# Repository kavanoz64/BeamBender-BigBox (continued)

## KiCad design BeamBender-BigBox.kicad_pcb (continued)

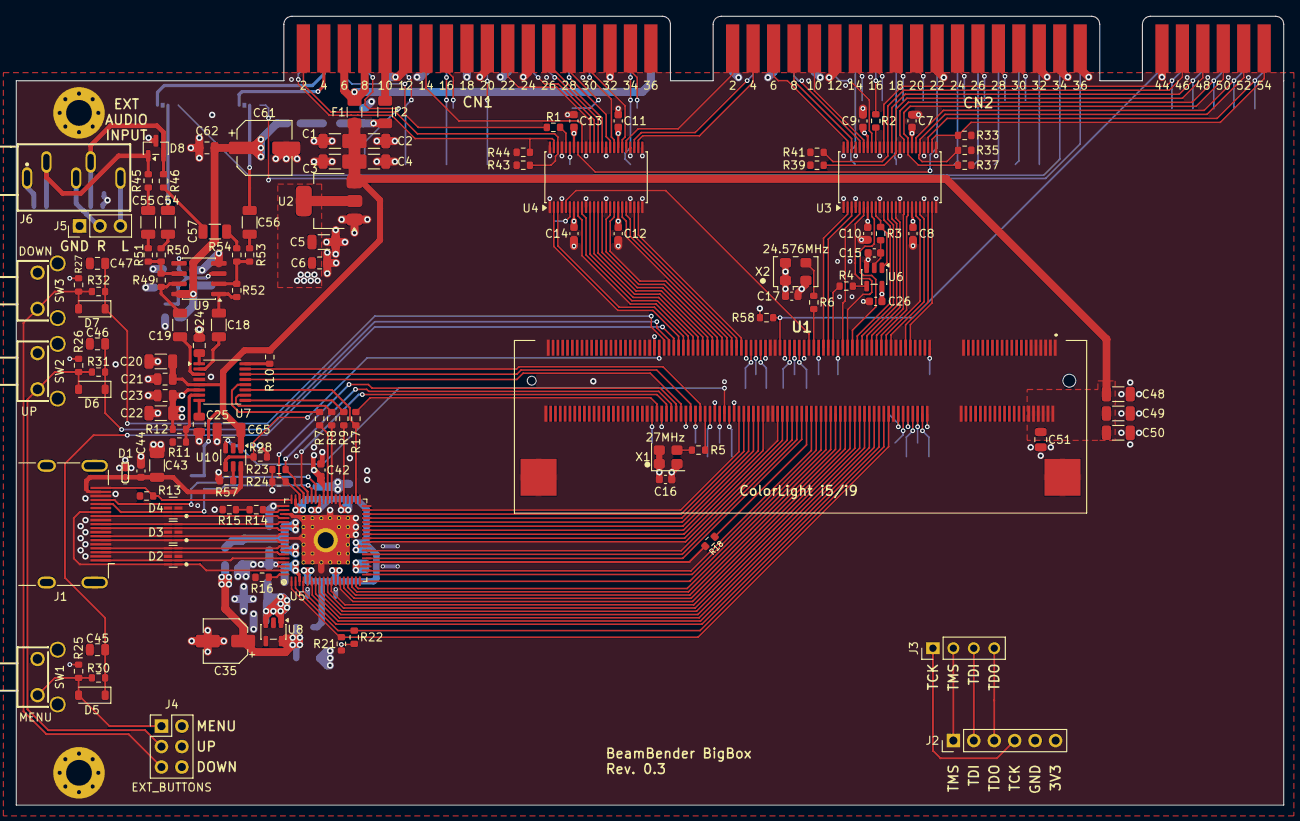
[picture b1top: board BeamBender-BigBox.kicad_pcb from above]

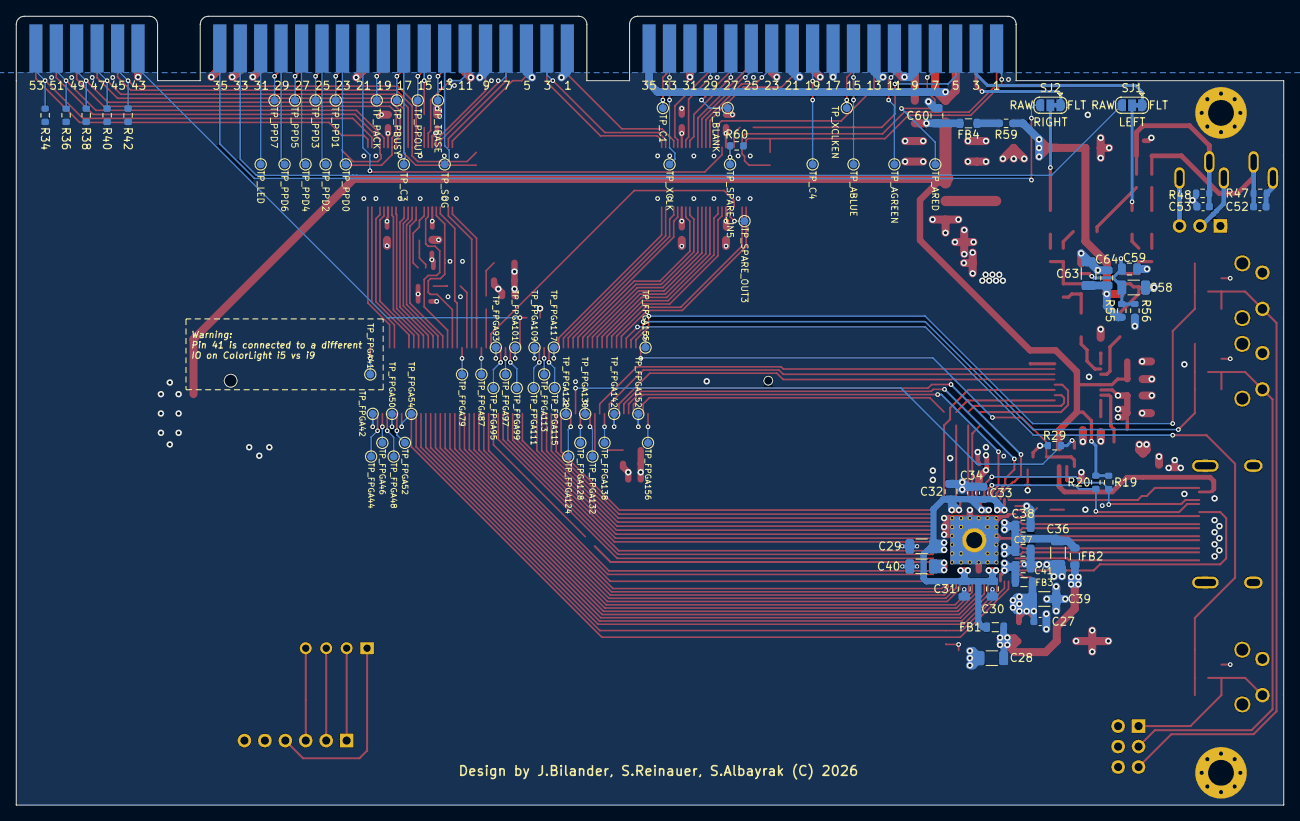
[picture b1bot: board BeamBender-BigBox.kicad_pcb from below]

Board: 4 copper layers, 157.5 x 98.0 mm, 221 parts (96 on the bottom side), 240 nets.

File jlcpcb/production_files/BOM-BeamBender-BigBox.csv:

Comment,Designator,Footprint,LCSC,Quantity
0,"R10,R60",R_0603_1608Metric,C21189,2
0.1A,F2,Fuse_1206_3216Metric,C2830236,1
100,"R45,R46",R_0603_1608Metric,C22775,2
100K,"R28,R33,R34,R35,R36,R37,R38,R39,R40,R41,R42,R43,R44,R47,R48",R_0603_1608Metric,C25803,15
100nF,"C10,C11,C12,C13,C14,C16,C17,C26,C33,C34,C42,C44,C7,C8,C9",C_0603_1608Metric,C14663,15
100nF 0805,"C21,C23,C30,C31,C32,C37,C38,C41,C45,C46,C47,C51,C59,C6,C60,C62,C64",C_0805_2012Metric,C28233,17
100nF 1206,"C29,C40",C_1206_3216Metric,C24497,2
10K,"R11,R13,R29,R30,R31,R32,R50,R53,R58",R_0603_1608Metric,C25804,9
10uF 1206,"C18,C19,C20,C22,C28,C36,C39,C4,C43,C5,C54,C55,C56,C57,C63,C65",C_1206_3216Metric,C96449,16
1K,"R15,R3,R59",R_0603_1608Metric,C21190,3
1N4148W,"D5,D6,D7",D_SOD-123,C81598,3
1uF,C27,C_0603_1608Metric,C15849,1
1uF 0805,C25,C_0805_2012Metric,C28323,1
2.5A,F1,Fuse_1206_3216Metric,C42449089,1
20K,"R51,R54",R_0603_1608Metric,C4184,2
220uF 25V,C61,CP_Elec_6.3x7.7,C190724,1
22pF,C15,C_0603_1608Metric,C1653,1
22uF 1206,"C1,C2,C3,C48,C49,C50,C58",C_1206_3216Metric,C90146,7
22uF 16V,C35,CP_Elec_5x5.8,C445073,1
2K,"R19,R20",R_0603_1608Metric,C22975,2
33,"R1,R17,R18,R2,R4,R5,R6,R7,R8,R9",R_0603_1608Metric,C23140,10
330pF C0G,"C52,C53",C_0603_1608Metric,C1664,2
3K3,R14,R_0603_1608Metric,C22978,1
470nF 0805,C24,C_0805_2012Metric,C13967,1
47K,"R55,R56",R_0603_1608Metric,C25819,2
4K7,"R16,R21,R22,R23,R24,R25,R26,R27",R_0603_1608Metric,C23162,8
56K,R57,R_0603_1608Metric,C23206,1
600R@100MHz 0.5A,"FB1,FB2,FB3,FB4",L_0805_2012Metric,C1017,4
74LVC16244ADGG,"U3,U4",TSSOP-48_6.1x12.5mm_P0.5mm,C6070,2
74LVC1G86,U6,SOT-23-5,C402161,1
8K2,"R49,R52",R_0603_1608Metric,C25981,2
AK5720VT,U7,TSSOP-16_4.4x5mm_P0.65mm,C1519002,1
AP2112K-1.2,U8,SOT-23-5,C460310,1
Colorlight-i5-v7.0,U1,1473149-4,C591654,1
D5V0F4U10LP-7,"D2,D3,D4",Diodes_UDFN-10_1.0x2.5mm_P0.5mm_HandSolder,C460833,3
DOWN,SW3,KEY-TH_TS-1038-A10B3-D2,C499341,1
EXT_BUTTONS,J4,PinHeader_2x03_P2.54mm_Vertical,C5383104,1
HDMI,J1,HDMI_A_Molex_208658-1001_Horizontal,C138388,1
JTAG,J2,PinHeader_1x06_P2.54mm_Vertical,C6332199,1
MENU,SW1,KEY-TH_TS-1038-A10B3-D2,C499341,1
OPA1692,U9,SOIC-8_3.9x4.9mm_P1.27mm,C2060550,1
Oscillator_3.2x2.5mm-27MHz,X1,Crystal_SMD_3225-4Pin_3.2x2.5mm,C37635418,1
Oscillator_5.0x3.2mm_24.576MHz,X2,Oscillator_SMD_EuroQuartz_XO53-4Pin_5.0x3.2mm,C2901534,1
SII9022ACNU,U5,QFN-72-1EP_10x10mm_P0.5mm_EP6x6mm_ThermalVias_HandSolder,C369565,1
SJ1-3535NG,J6,AUDIO-TH_SJ1-3535NG,C4991610,1
SP1003-01DTG,D1,SOD-723_L1.0-W0.6-LS1.4-RD,C126834,1
TLV76133DCYR,U2,SOT-223-3_TabPin2,C7527500,1
TPD2E009,D8,SOT-23,C2871371,1
TPS2553DBVR,U10,SOT-23-6,C55266,1
UP,SW2,KEY-TH_TS-1038-A10B3-D2,C499341,1
XAUDIO,J5,PinHeader_1x03_P2.54mm_Vertical,C5383112,1

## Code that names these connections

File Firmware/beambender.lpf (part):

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BLOCK ASYNCPATHS;

# ---- Clocks ------------------------------------------------------
LOCATE COMP "clk_c28o" SITE "J19";                  # pin 91  C28O_3V3
LOCATE COMP "clk_14m" SITE "L20";                   # pin 81  14M_3V3
LOCATE COMP "clk_27m" SITE "G3";                    # pin 134 XTAL_27M
LOCATE COMP "clk_24m576" SITE "J20";                # pin 89  XTAL_24.576M

# ---- Amiga video input (via 74LVC16244) --------------------------
LOCATE COMP "amiga_r[0]" SITE "C1";                 # pin 145 R0_3V3
LOCATE COMP "amiga_r[1]" SITE "B1";                 # pin 143 R1_3V3
LOCATE COMP "amiga_r[2]" SITE "U17";                # pin 71  R2_3V3
LOCATE COMP "amiga_r[3]" SITE "U18";                # pin 69  R3_3V3
LOCATE COMP "amiga_r[4]" SITE "A19";                # pin 123 R4_3V3
LOCATE COMP "amiga_r[5]" SITE "B18";                # pin 121 R5_3V3
LOCATE COMP "amiga_r[6]" SITE "B19";                # pin 119 R6_3V3
LOCATE COMP "amiga_r[7]" SITE "A18";                # pin 127 R7_3V3
LOCATE COMP "amiga_g[0]" SITE "T17";                # pin 67  G0_3V3
LOCATE COMP "amiga_g[1]" SITE "M17";                # pin 65  G1_3V3
LOCATE COMP "amiga_g[2]" SITE "P17";                # pin 63  G2_3V3
LOCATE COMP "amiga_g[3]" SITE "R17";                # pin 61  G3_3V3
LOCATE COMP "amiga_g[4]" SITE "K20";                # pin 85  G4_3V3
LOCATE COMP "amiga_g[5]" SITE "N18";                # pin 77  G5_3V3
LOCATE COMP "amiga_g[6]" SITE "L18";                # pin 83  G6_3V3
LOCATE COMP "amiga_g[7]" SITE "D3";                 # pin 129 G7_3V3
LOCATE COMP "amiga_b[0]" SITE "R18";                # pin 59  B0_3V3
LOCATE COMP "amiga_b[1]" SITE "T18";                # pin 57  B1_3V3
LOCATE COMP "amiga_b[2]" SITE "C18";                # pin 51  B2_3V3
LOCATE COMP "amiga_b[3]" SITE "K18";                # pin 49  B3_3V3
LOCATE COMP "amiga_b[4]" SITE "C3";                 # pin 135 B4_3V3
LOCATE COMP "amiga_b[5]" SITE "N17";                # pin 75  B5_3V3
LOCATE COMP "amiga_b[6]" SITE "P18";                # pin 73  B6_3V3
LOCATE COMP "amiga_b[7]" SITE "B4";                 # pin 133 B7_3V3
LOCATE COMP "amiga_hsync_n" SITE "E3";              # pin 137 HSYNC_3V3
LOCATE COMP "amiga_vsync_n" SITE "C4";              # pin 131 VSYNC_3V3
LOCATE COMP "amiga_csync_n" SITE "A3";              # pin 139 CSYNC_3V3
LOCATE COMP "amiga_pixelsw" SITE "C17";             # pin 125 PIXELSW_3V3
LOCATE COMP "amiga_psel" SITE "C2";                 # pin 141 PSEL_3V3

# ---- Machine detect ----------------------------------------------
LOCATE COMP "aga_detect" SITE "E20";                # pin 103 AGA_DETECT

# ---- OSD buttons -------------------------------------------------
LOCATE COMP "btn_1" SITE "D2";                      # pin 147 BT1_INPUT
LOCATE COMP "btn_2" SITE "D1";                      # pin 149 BT2_INPUT
LOCATE COMP "btn_3" SITE "E2";                      # pin 151 BT3_INPUT

# ---- HDMI transmitter (SiI9022A) ---------------------------------
LOCATE COMP "hdmi_r[0]" SITE "L5";                  # pin 76  R0_FPGA
LOCATE COMP "hdmi_r[1]" SITE "L4";                  # pin 74  R1_FPGA
LOCATE COMP "hdmi_r[2]" SITE "M4";                  # pin 72  R2_FPGA
LOCATE COMP "hdmi_r[3]" SITE "N4";                  # pin 70  R3_FPGA
LOCATE COMP "hdmi_r[4]" SITE "R3";                  # pin 68  R4_FPGA
LOCATE COMP "hdmi_r[5]" SITE "T3";                  # pin 66  R5_FPGA
LOCATE COMP "hdmi_r[6]" SITE "M3";                  # pin 64  R6_FPGA
LOCATE COMP "hdmi_r[7]" SITE "T2";                  # pin 62  R7_FPGA
LOCATE COMP "hdmi_g[0]" SITE "F18";                 # pin 94  G0_FPGA
LOCATE COMP "hdmi_g[1]" SITE "G18";                 # pin 90  G1_FPGA
LOCATE COMP "hdmi_g[2]" SITE "H17";                 # pin 88  G2_FPGA
LOCATE COMP "hdmi_g[3]" SITE "H18";                 # pin 86  G3_FPGA
LOCATE COMP "hdmi_g[4]" SITE "J17";                 # pin 84  G4_FPGA
LOCATE COMP "hdmi_g[5]" SITE "J18";                 # pin 82  G5_FPGA
LOCATE COMP "hdmi_g[6]" SITE "J16";                 # pin 80  G6_FPGA
LOCATE COMP "hdmi_g[7]" SITE "P16";                 # pin 78  G7_FPGA
LOCATE COMP "hdmi_b[0]" SITE "D17";                 # pin 114 B0_FPGA
LOCATE COMP "hdmi_b[1]" SITE "D18";                 # pin 112 B1_FPGA
LOCATE COMP "hdmi_b[2]" SITE "E17";                 # pin 110 B2_FPGA
LOCATE COMP "hdmi_b[3]" SITE "E16";                 # pin 104 B3_FPGA
LOCATE COMP "hdmi_b[4]" SITE "F16";                 # pin 102 B4_FPGA
LOCATE COMP "hdmi_b[5]" SITE "F17";                 # pin 100 B5_FPGA
LOCATE COMP "hdmi_b[6]" SITE "E18";                 # pin 98  B6_FPGA
LOCATE COMP "hdmi_b[7]" SITE "G16";                 # pin 96  B7_FPGA
LOCATE COMP "hdmi_pclk" SITE "H16";                 # pin 92  /PIXEL_CLK
LOCATE COMP "hdmi_de" SITE "G5";                    # pin 116 DE
LOCATE COMP "hdmi_hsync" SITE "D16";                # pin 118 HSYNC_FPGA
LOCATE COMP "hdmi_vsync" SITE "F5";                 # pin 120 VSYNC_FPGA
LOCATE COMP "hdmi_reset_n" SITE "K4";               # pin 148 HDMI_RESET
LOCATE COMP "hdmi_int_n" SITE "K3";                 # pin 146 INT
LOCATE COMP "hdmi_cec" SITE "K5";                   # pin 150 CEC_D

# ---- HDMI +5V load switch (TPS2553) ------------------------------
LOCATE COMP "hdmi_pwr_en" SITE "F4";                # pin 126 HDMI_EN
LOCATE COMP "hdmi_fault_n" SITE "E1";               # pin 153 HDMI_FAULT

# ---- I2C (SiI9022A control) --------------------------------------
LOCATE COMP "i2c_scl" SITE "N2";                    # pin 58  SCL_I2C
LOCATE COMP "i2c_sda" SITE "N3";                    # pin 60  SDA_I2C

# ---- Audio ADC (AK5720) - config only, no I2S data path ----------
LOCATE COMP "adc_mclk" SITE "A2";                   # pin 154 /MCLK_OUT
LOCATE COMP "adc_reset_n" SITE "J5";                # pin 144 PDN_RESET_N
LOCATE COMP "adc_fsel" SITE "H3";                   # pin 136 FSEL
LOCATE COMP "adc_dif" SITE "H5";                    # pin 140 DIF|TDMI

# ---- I/O standard ------------------------------------------------------
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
